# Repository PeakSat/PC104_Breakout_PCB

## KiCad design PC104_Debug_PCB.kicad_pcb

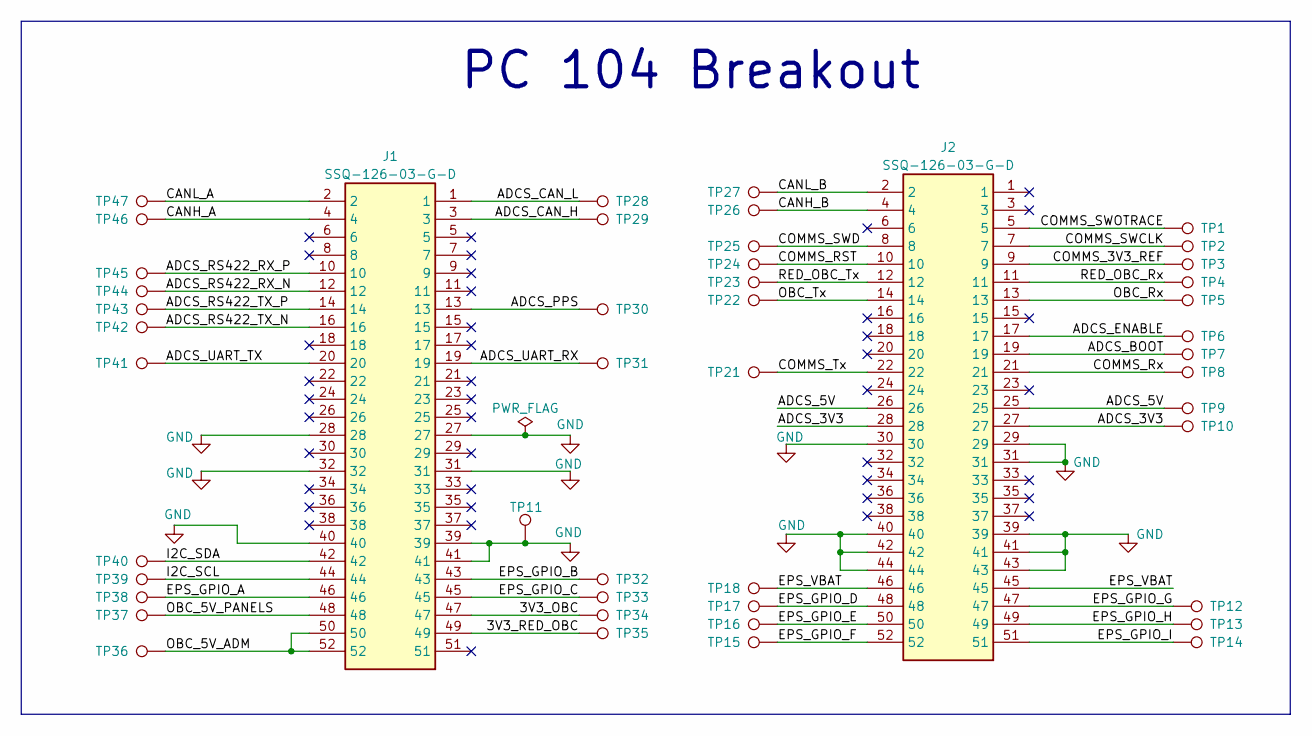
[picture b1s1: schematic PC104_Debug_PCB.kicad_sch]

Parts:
J1, J2: SSQ-126-03-G-D; SSQ-126-XX-YYY-D; Mouser Part Number 200-SSQ12603GD
TP1, TP2, TP3, TP4, TP5, TP6, TP7, TP8, TP9, TP10, TP11, TP12, TP13, TP14, TP15, TP16, TP17, TP18, TP21, TP22, TP23, TP24, TP25, TP26, TP27, TP28, TP29, TP30, TP31, TP32, TP33, TP34, TP35, TP36, TP37, TP38, TP39, TP40, TP41, TP42, TP43, TP44, TP45, TP46, TP47: TestPoint; TestPoint_Plated_Hole_D2.0mm

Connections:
/3V3_OBC: J1.47, TP34.1
/3V3_RED_OBC: J1.49, TP35.1
/ADCS_3V3: J2.27, J2.28, TP10.1
/ADCS_5V: J2.25, J2.26, TP9.1
/ADCS_BOOT: J2.19, TP7.1
/ADCS_CAN_H: J1.3, TP29.1
/ADCS_CAN_L: J1.1, TP28.1
/ADCS_ENABLE: J2.17, TP6.1
/ADCS_PPS: J1.13, TP30.1
/ADCS_RS422_RX_N: J1.12, TP44.1
/ADCS_RS422_RX_P: J1.10, TP45.1
/ADCS_RS422_TX_N: J1.16, TP42.1
/ADCS_RS422_TX_P: J1.14, TP43.1
/ADCS_UART_RX: J1.19, TP31.1
/ADCS_UART_TX: J1.20, TP41.1
/CANH_A: J1.4, TP46.1
/CANH_B: J2.4, TP26.1
/CANL_A: J1.2, TP47.1
/CANL_B: J2.2, TP27.1
/COMMS_3V3_REF: J2.9, TP3.1
/COMMS_RST: J2.10, TP24.1
/COMMS_Rx: J2.21, TP8.1
/COMMS_SWCLK: J2.7, TP2.1
/COMMS_SWD: J2.8, TP25.1
/COMMS_SWOTRACE: J2.5, TP1.1
/COMMS_Tx: J2.22, TP21.1
/EPS_GPIO_A: J1.46, TP38.1
/EPS_GPIO_B: J1.43, TP32.1
/EPS_GPIO_C: J1.45, TP33.1
/EPS_GPIO_D: J2.48, TP17.1
/EPS_GPIO_E: J2.50, TP16.1
/EPS_GPIO_F: J2.52, TP15.1
/EPS_GPIO_G: J2.47, TP12.1
/EPS_GPIO_H: J2.49, TP13.1
/EPS_GPIO_I: J2.51, TP14.1
/EPS_VBAT: J2.45, J2.46, TP18.1
/I2C_SCL: J1.44, TP39.1
/I2C_SDA: J1.42, TP40.1
/OBC_5V_ADM: J1.50, J1.52, TP36.1
/OBC_5V_PANELS: J1.48, TP37.1
/OBC_Rx: J2.13, TP5.1
/OBC_Tx: J2.14, TP22.1
/RED_OBC_Rx: J2.11, TP4.1
/RED_OBC_Tx: J2.12, TP23.1
GND: J1.27, J1.28, J1.31, J1.32, J1.39, J1.40, J1.41, J2.29, J2.30, J2.31, J2.39, J2.40, J2.41, J2.42, J2.43, J2.44, TP11.1

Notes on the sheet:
PC 104 Breakout

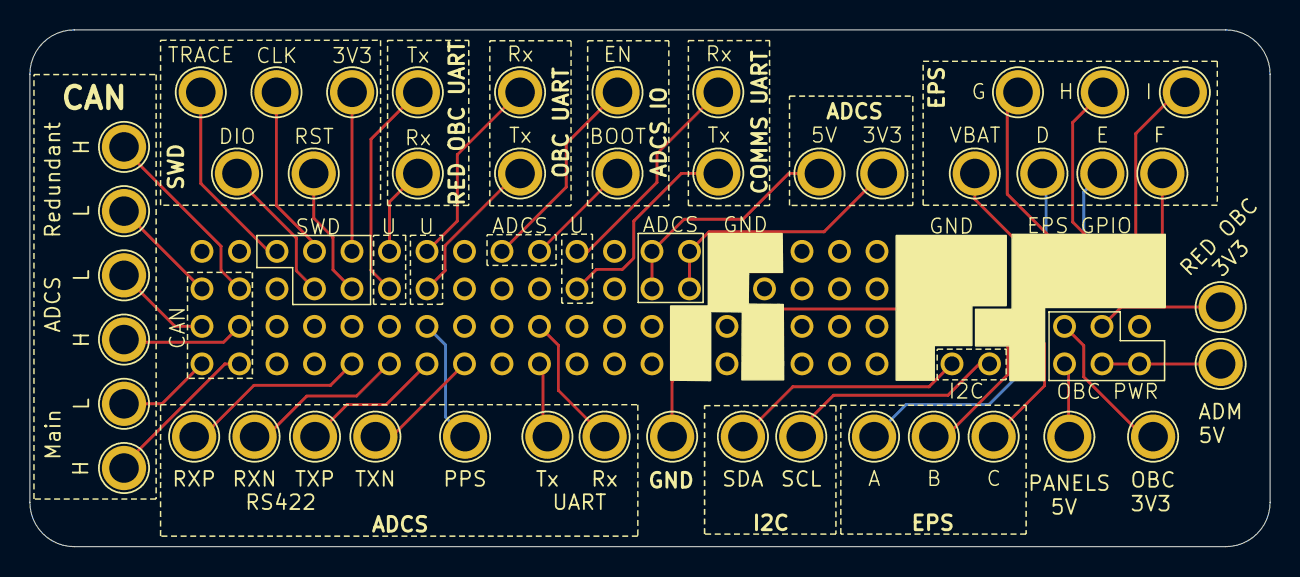
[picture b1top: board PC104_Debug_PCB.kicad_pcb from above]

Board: 2 copper layers, 84.0 x 35.0 mm, 47 parts (0 on the bottom side), 45 nets.

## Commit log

2024-11-06 v1.0
2024-11-08 Fixed PCB dimensions
2024-11-11 Added Manufacture files
